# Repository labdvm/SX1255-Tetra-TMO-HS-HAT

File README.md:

# SX1255--HAT's

# Little PA HAT you can order from here:
- 

This is modified SXceiver, thanks to Tatu Peltola for shared schematic.
# Two versions of HAT's: HAT with (LPF_TX, BPF_RX filters and PA) and HAT with (LPF_TX, BPF_RX filters without PA) and added SPI line protection IC. The first HAT also is known as "Little PA".
# The PA (TQP3M9036) can amplify up to ~25dBm @ (70cm-band) 
# I can make Custom design too. (pclab.mk@gmail.com)
# RPi 4/5, fast-write micro-sd card or upgraded with M.2 nvme drive.
# The eeprom is for HW-ID " https://github.com/tejeez/sxxcvr/blob/main/dts/README.md ".
# For Tetra-TMO Base Station this is the installing procedures, " https://github.com/MidnightBlueLabs/tetra-bluestation-docs/wiki ".
# BlueStation, https://github.com/MidnightBlueLabs/tetra-bluestation
# BlueStation Tetra TMO configurator " https://bluestation.russel053.com/ "
# FlowStation, https://github.com/razvanzeces/flowstation
# Nexus-BS, https://github.com/invictus737/nexus-bs

Install FlowStation ---for sxceiver---
# 1. Install Trixie 64bit-LITE
2. Install lib's:
# sudo apt update
# sudo apt install git make g++ cmake
# sudo apt install libsoapysdr-dev
# sudo apt install soapysdr-tools
# sudo apt install libasound2-dev
# sudo apt install clang llvm-dev libclang-dev

3. Install Rust:
# curl https://sh.rustup.rs -sSf | sh

4. RPi-setup:
"enable SPI and I2C"
# sudo raspi-config > Interface Options > "enable and reboot the rpi"
# sudo nano /boot/firmware/config.txt
"add"
# dtparam=i2c_vc=on
"Reboot the Rpi"

5. Install SoapySX:
# cd
# git clone "https://github.com/tejeez/sxxcvr.git"
# cd sxxcvr/SoapySX
# mkdir build
# cd build
# cmake ..
# make
# sudo make install
# sudo ldconfig

Check that the driver is available:
# SoapySDRUtil --info

Check that the device is detected:
# ls -l /proc/device-tree/hat
# SoapySDRUtil --probe=driver=sx

6. Install The FlowStation:
# git clone https://github.com/razvanzeces/flowstation
# cd flowstation
# . "$HOME/.cargo/env"
# cargo build --release (or cargo build --release -j1)
# cp example_config/config.toml config.toml
# nano config.toml "configure the base station"
- After configured "config.toml" make a fallback copy
# cp config.toml config.toml.fallback

7. Run:
# cd flowstation
# ./target/release/bluestation-bs ./config.toml

8. Update:
# git pull
# cargo build --release

# Z32IT

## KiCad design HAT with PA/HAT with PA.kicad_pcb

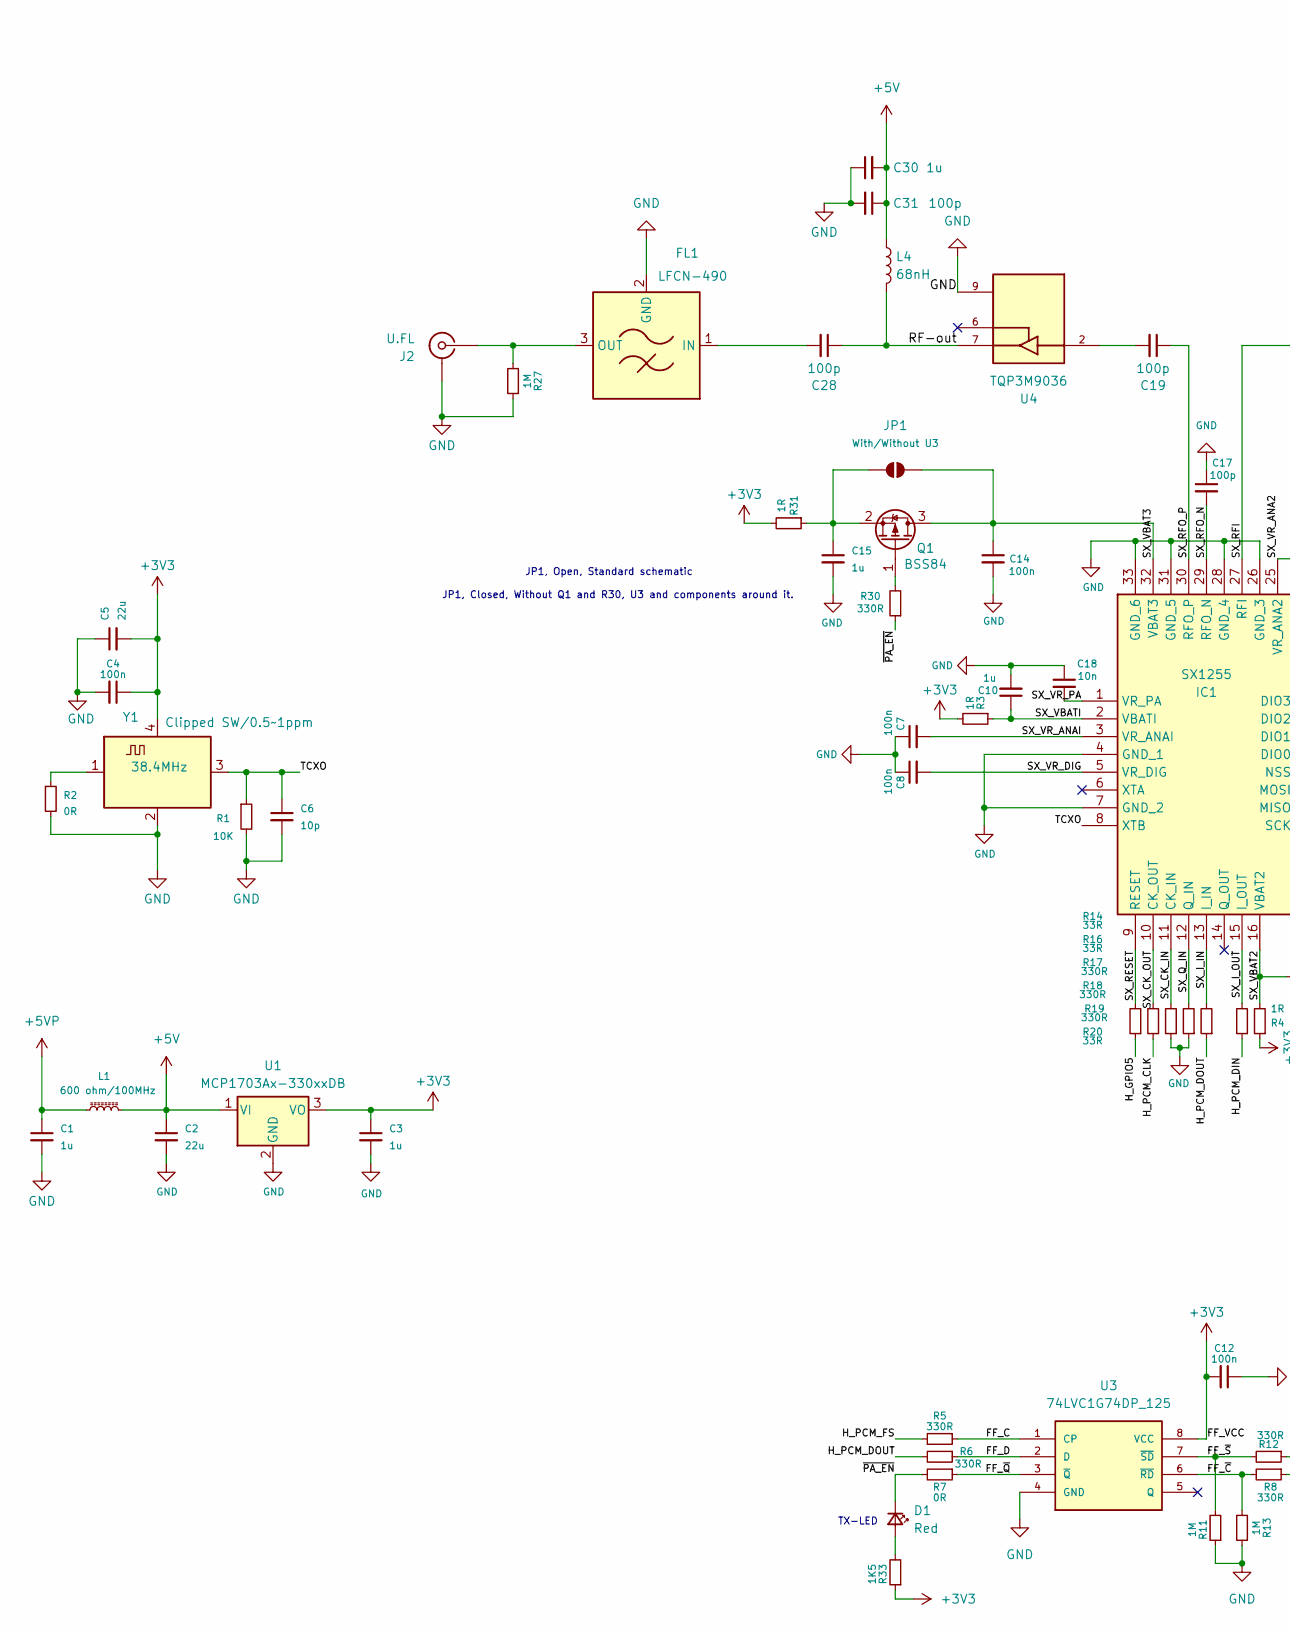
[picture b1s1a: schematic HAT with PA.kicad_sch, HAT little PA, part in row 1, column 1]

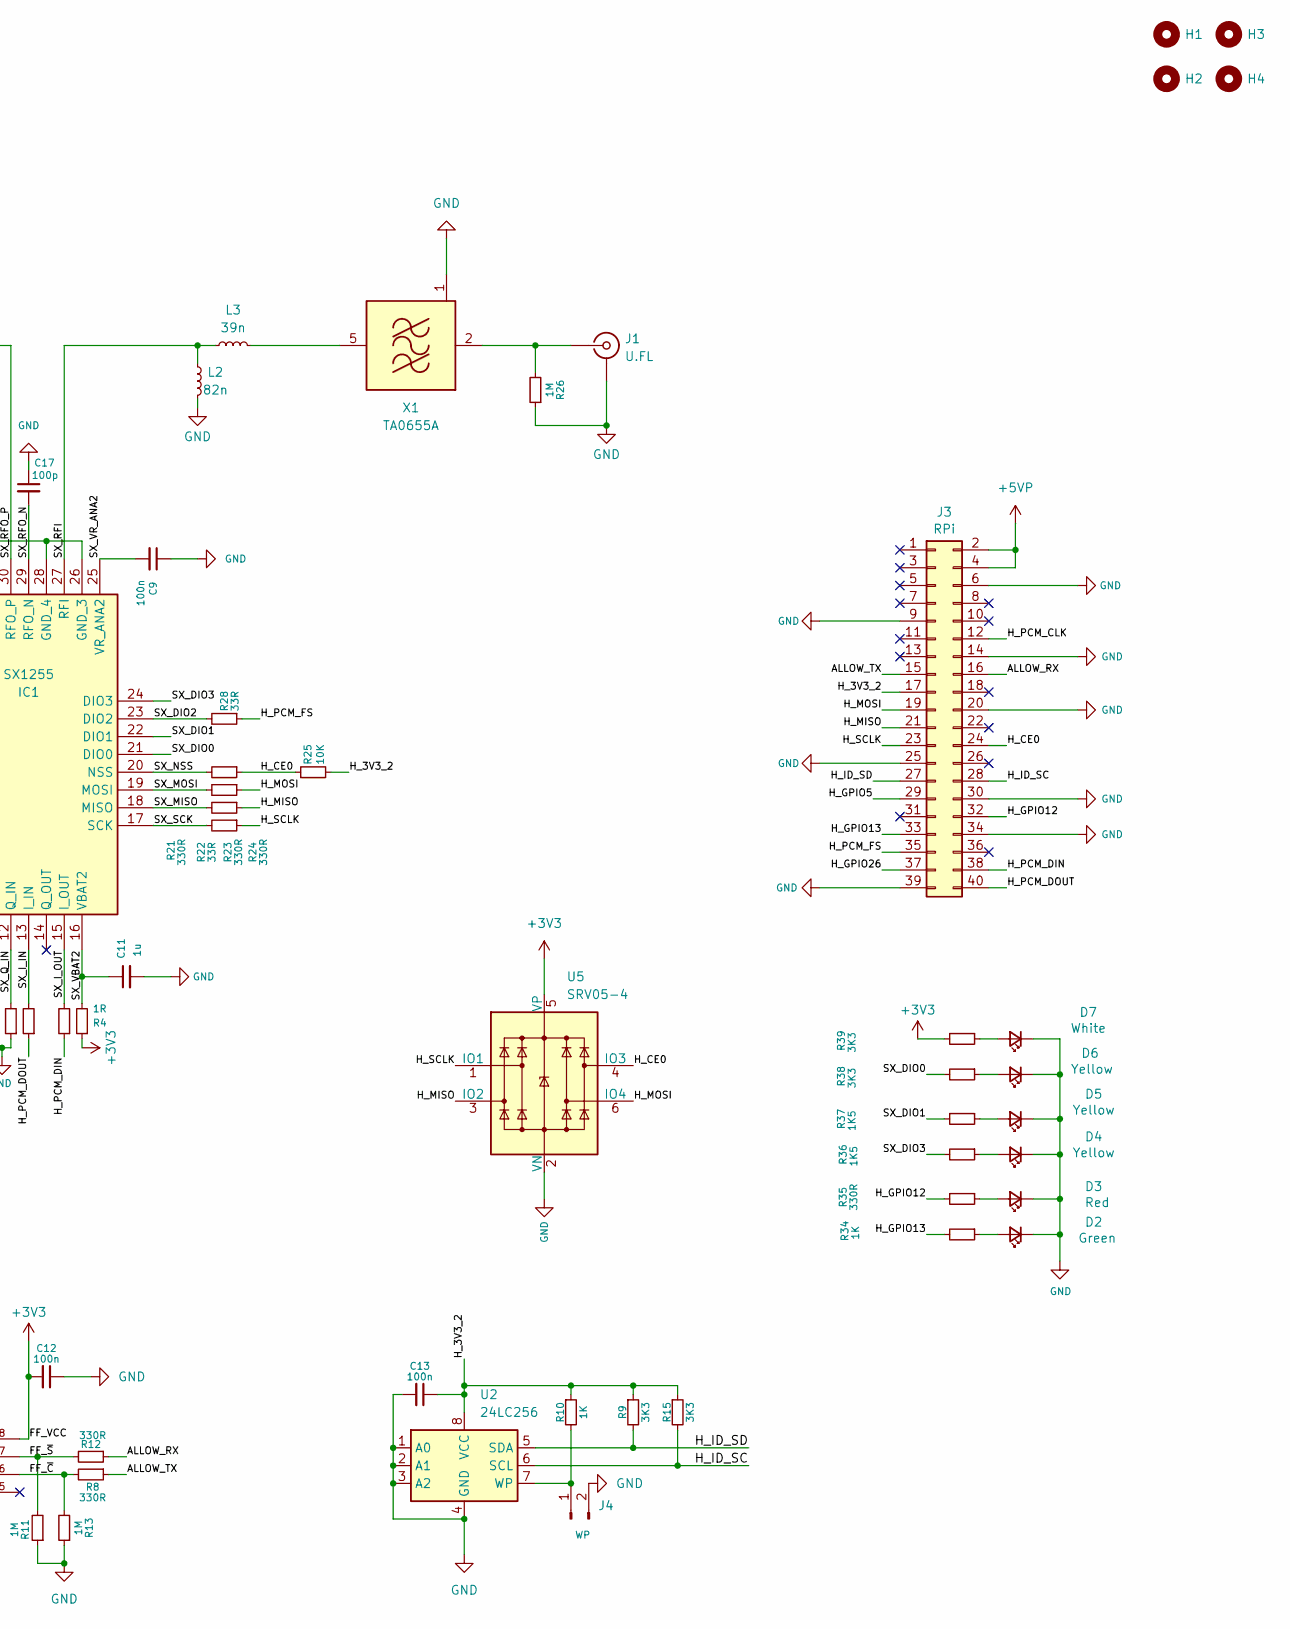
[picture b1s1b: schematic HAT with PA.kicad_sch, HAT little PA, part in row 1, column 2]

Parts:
C1, C3, C10, C11, C15, C30: 1u; C_0603_1608Metric; Part Number 311-3484-1-ND
C2, C5: 22u; C_1206_3216Metric; Part Number 1276-3148-1-ND
C4, C7, C8, C9, C12, C13, C14: 100n; C_0603_1608Metric; Part Number 720-1688-1-ND
C6: 10p; C_0603_1608Metric; Part Number 399-14932-1-ND
C17, C19, C28, C31: 100p; C_0603_1608Metric; Part Number 399-15348-1-ND
C18: 10n; C_0603_1608Metric; Part Number 399-C0603C103K8RACTUCT-ND
D1, D3: Red; LED_0603_1608Metric_Pad1.05x0.95mm_HandSolder; Part Number 160-1479-1-ND
D2: Green; LED_0603_1608Metric_Pad1.05x0.95mm_HandSolder; Part Number 754-APT1608SGD3CT-ND
D4, D5, D6: Yellow; LED_0603_1608Metric_Pad1.05x0.95mm_HandSolder; Part Number 160-1437-1-ND
D7: White; LED_0603_1608Metric_Pad1.05x0.95mm_HandSolder; Part Number 160-LTST-T180UWETCT-ND
FL1: LFCN-490; Filter_Mini-Circuits_FV1206; Part Number 3157-LFCN-490+CT-ND
H1, H2, H3, H4: MountingHole; MountingHole_2.7mm_M2.5_DIN965
IC1: SX1255; QFN50P500X500X80-33N-D; Part Number SX1255IWLTRTCT-ND
J1, J2: U.FL; Part Number 343-CONMHF1-SMD-G-TCT-ND
J3: RPi; PinSocket_2x20_P2.54mm_Vertical
J4: WP; PinHeader_1x02_P2.54mm_Vertical
JP1: With/Without U3; SolderJumper-2_P1.3mm_Open_RoundedPad1.0x1.5mm
L1: 600 ohm/100MHz; L_0805_2012Metric; Part Number 490-1046-1-ND
L2: 82n; L_0603_1608Metric; Part Number 712-LRC0603CJ82NGV001TCT-ND
L3: 39n; L_0603_1608Metric; Part Number 712-LRC0603CJ39NGV001TCT-ND
L4: 68nH; L_0603_1608Metric; Part Number 712-LRC0603CJ68NGV001TCT-ND
Q1: BSS84; SOT-23; Part Number 3372-BSS84TR-ND
R1, R25: 10K; R_0603_1608Metric; Part Number 541-10.0KHCT-ND
R2, R7: 0R; R_0603_1608Metric; Part Number 541-0.0GCT-ND
R3, R4, R31: 1R; R_0603_1608Metric; Part Number 541-1.00HHCT-ND
R5, R6, R8, R12, R17, R18, R19, R21, R23, R24, R30, R35: 330R; R_0603_1608Metric; Part Number 541-330HCT-ND
R9, R15, R38, R39: 3K3; R_0603_1608Metric; Part Number 541-3.30KHCT-ND
R10, R34: 1K; R_0603_1608Metric; Part Number 541-1.00KHCT-ND
R11, R13, R26, R27: 1M; R_0603_1608Metric; Part Number 541-1.00MHCT-ND
R14, R16, R20, R22, R28: 33R; R_0603_1608Metric; Part Number 541-33.0HCT-ND
R33, R36, R37: 1K5; R_0603_1608Metric; Part Number 541-1.5KGCT-ND
U1: MCP1703Ax-330xxDB; SOT-223-3_TabPin2; Part Number MCP1703T-3302E/DBCT-ND
U2: 24LC256; SOIC-8_3.9x4.9mm_P1.27mm; Part Number 24LC256-I/SN-ND
U3: 74LVC1G74DP_125; SOP65P400X110-8N; Part Number 1727-5983-1-ND
U4: TQP3M9036; SON50P200X200X95-9N; Part Number 2312-TQP3M9036CT-ND
U5: SRV05-4; SOT-23-6_Handsoldering; DigiKey Part Number SRV05-4CT-ND
X1: TA0655A; Filter_SAW-6_3.8x3.8mm
Y1: 38.4MHz; Crystal_SMD_3225-4Pin_3.2x2.5mm; Part Number 114-TG2520SMN38.4000M-MCGNNM3CT-ND

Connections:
+3V3: C3.1, C4.1, C5.2, C12.2, R3.2, R4.1, R31.2, R33.1, R39.2, U1.3 (VO), U3.8 (VCC), U5.5 (VP), Y1.4 (VDD)
+5V: C2.1, C30.2, C31.1, L1.2, L4.1, U1.1 (VI)
+5VP: C1.1, J3.2, J3.4, L1.1
/ALLOW_RX: J3.16, R12.1
/ALLOW_TX: J3.15, R8.1
/FF_C: R5.1, U3.1 (CP)
/FF_D: R6.1, U3.2 (D)
/FF_~C: R8.2, R13.2, U3.6 (~RD)
/FF_~Q: R7.1, U3.3 (~Q)
/FF_~S: R11.2, R12.2, U3.7 (~SD)
/H_3V3_2: C13.1, J3.17, R9.1, R10.1, R15.1, R25.2, U2.8 (VCC)
/H_CE0: J3.24, R24.1, R25.1, U5.4 (IO3)
/H_GPIO5: J3.29, R14.1
/H_GPIO12: J3.32, R35.2
/H_GPIO13: J3.33, R34.2
/H_GPIO26: J3.37
/H_ID_SC: J3.28, R15.2, U2.6 (SCL)
/H_ID_SD: J3.27, R9.2, U2.5 (SDA)
/H_MISO: J3.21, R22.1, U5.3 (IO2)
/H_MOSI: J3.19, R23.1, U5.6 (IO4)
/H_PCM_CLK: J3.12, R16.1
/H_PCM_DIN: J3.38, R20.1
/H_PCM_DOUT: J3.40, R6.2, R19.1
/H_PCM_FS: J3.35, R5.2, R28.1
/H_SCLK: J3.23, R21.1, U5.1 (IO1)
/RF-out: C28.1, L4.2, U4.7
/SX_CK_IN: IC1.11 (CK_IN), R17.2
/SX_CK_OUT: IC1.10 (CK_OUT), R16.2
/SX_DIO0: IC1.21 (DIO0), R38.2
/SX_DIO1: IC1.22 (DIO1), R37.2
/SX_DIO2: IC1.23 (DIO2), R28.2
/SX_DIO3: IC1.24 (DIO3), R36.2
/SX_I_IN: IC1.13 (I_IN), R19.2
/SX_I_OUT: IC1.15 (I_OUT), R20.2
/SX_MISO: IC1.18 (MISO), R22.2
/SX_MOSI: IC1.19 (MOSI), R23.2
/SX_NSS: IC1.20 (NSS), R24.2
/SX_Q_IN: IC1.12 (Q_IN), R18.2
/SX_RESET: IC1.9 (RESET), R14.2
/SX_RFI: IC1.27 (RFI), L2.2, L3.2
/SX_RFO_N: C17.2, IC1.29 (RFO_N)
/SX_RFO_P: C19.1, IC1.30 (RFO_P)
/SX_SCK: IC1.17 (SCK), R21.2
/SX_VBAT2: C11.1, IC1.16 (VBAT2), R4.2
/SX_VBAT3: C14.1, IC1.32 (VBAT3), JP1.2 (B), Q1.3 (D)
/SX_VBATI: C10.1, IC1.2 (VBATI), R3.1
/SX_VR_ANA2: C9.2, IC1.25 (VR_ANA2)
/SX_VR_ANAI: C7.2, IC1.3 (VR_ANAI)
/SX_VR_DIG: C8.2, IC1.5 (VR_DIG)
/SX_VR_PA: C18.2, IC1.1 (VR_PA)
/TCXO: C6.1, IC1.8 (XTB), R1.1, Y1.3 (OUT)
/~PA_EN: D1.1 (K), R7.2, R30.1
GND: C1.2, C2.2, C3.2, C4.2, C5.1, C6.2, C7.1, C8.1, C9.1, C10.2, C11.2, C12.1, C13.2, C14.2, C15.2, C17.1, C18.1, C30.1, C31.2, D2.1 (K), D3.1 (K), D4.1 (K), D5.1 (K), D6.1 (K), D7.1 (K), FL1.2 (GND), FL1.4 (GND), IC1.4 (GND_1), IC1.7 (GND_2), IC1.26 (GND_3), IC1.28 (GND_4), IC1.31 (GND_5), IC1.33 (GND_6), J1.2 (Ext), J2.2 (Ext), J3.6, J3.9, J3.14, J3.20, J3.25, J3.30, J3.34, J3.39, J4.2, L2.1, R1.2, R2.2, R11.1, R13.1, R17.1, R18.1, R26.1, R27.1, U1.2 (GND), U2.1 (A0), U2.2 (A1), U2.3 (A2), U2.4 (GND), U3.4 (GND), U4.1, U4.3, U4.4, U4.5, U4.8, U4.9, U4.V1, U4.V2, U4.V3, U5.2 (VN), X1.1 (GND), X1.3 (GND), X1.4 (GND), X1.6 (GND), Y1.2 (GND)
unnamed: C19.2, U4.2
unnamed: D1.2 (A), R33.2
unnamed: D2.2 (A), R34.1
unnamed: D3.2 (A), R35.1
unnamed: D4.2 (A), R36.1
unnamed: D5.2 (A), R37.1
unnamed: D6.2 (A), R38.1
unnamed: D7.2 (A), R39.1
unnamed: C28.2, FL1.1 (IN)
unnamed: FL1.3 (OUT), J2.1 (In), R27.2
unnamed: J1.1 (In), R26.2, X1.2 (IN)
unnamed: J4.1, R10.2, U2.7 (WP)
unnamed: C15.1, JP1.1 (A), Q1.2 (S), R31.1
unnamed: Q1.1 (G), R30.2
unnamed: L3.1, X1.5 (OUT)
unnamed: R2.1, Y1.1 (Tri-State)

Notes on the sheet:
JP1, Closed, Without Q1 and R30, U3 and components around it.
JP1, Open, Standard schematic
TX-LED

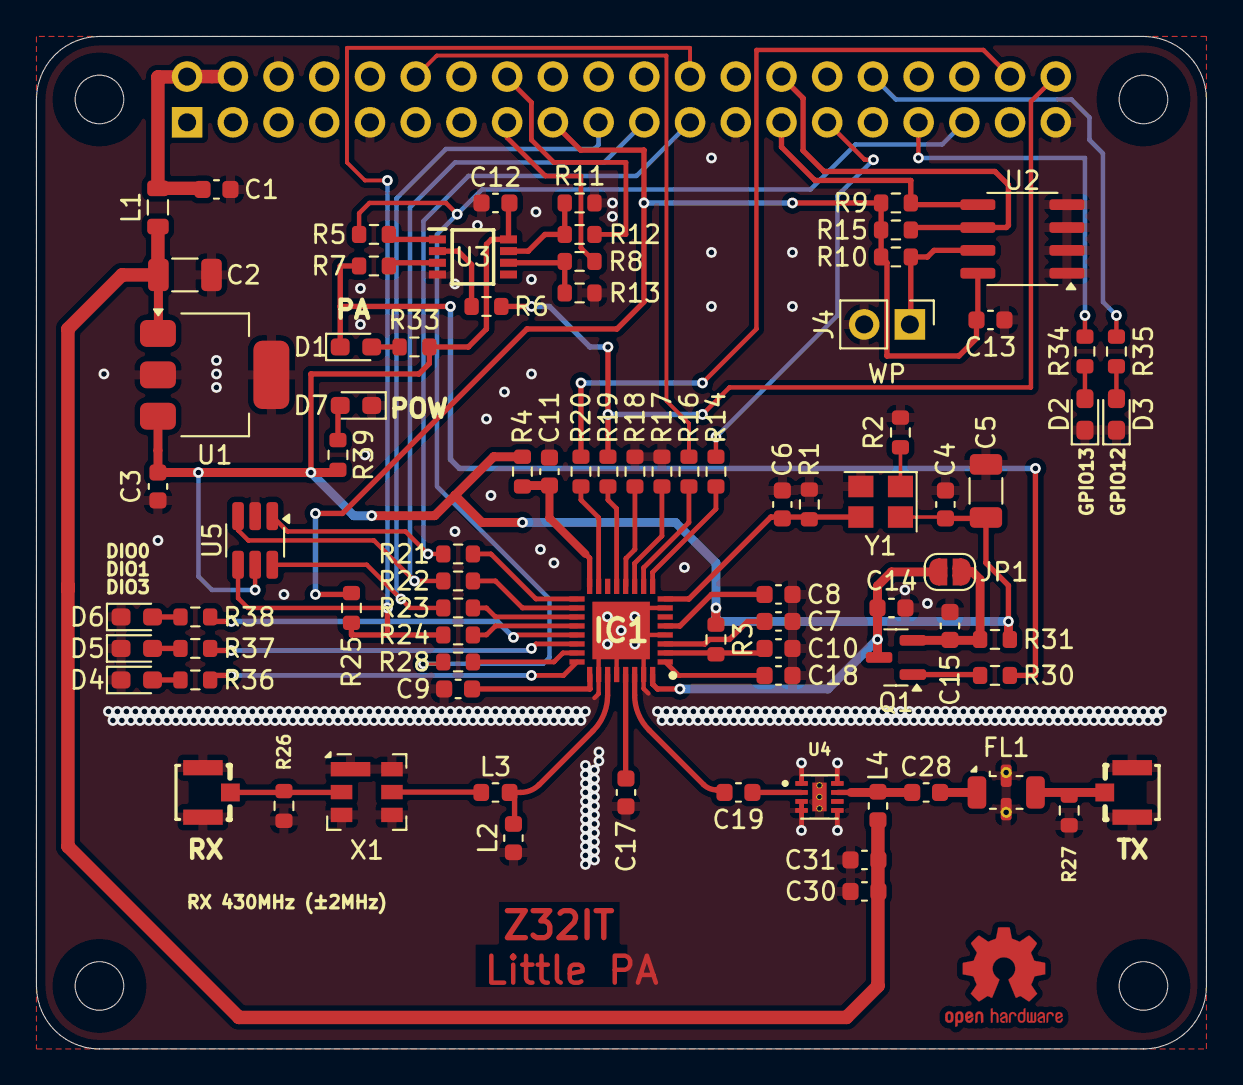
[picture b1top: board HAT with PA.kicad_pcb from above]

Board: 2 copper layers, 65.0 x 56.2 mm, 88 parts (1 on the bottom side), 68 nets.

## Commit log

2026-03-16 Revise README for SX1255-HAT details and credits
    Updated README to clarify SX1255-HAT versions and credit Tatu Peltola.
2026-03-16 Update HAT descriptions for clarity
    Clarified descriptions of the three versions of HATs for better readability.
2026-03-20 Update README to simplify RPi4/5 requirements
    Removed the mention of minimum RAM requirement for RPi4/5.
2026-03-24 Update README to reflect four versions of HAT
2026-03-25 Add custom design services note to README
    Added a note about custom design services.
2026-03-30 Update HAT versions description in README
2026-03-30 Update filter types in README for HAT versions
2026-03-30 Add donation information to README
    Added donation link for project support.
2026-04-10 Update BlueStation Tetra TMO configurator URL
2026-05-04 Update PA amplification value to 25dBm
2026-05-12 Update README with FlowStation installation steps
    Added installation instructions for FlowStation and related dependencies.
2026-05-14 Remove donation link from README
    Removed donation link from the README.
2026-06-02 Update README with additional information on HAT versions
    Added clarification about the first HAT being known as 'Little PA'.
2026-06-15 Revise README for installation steps and clarity
    Updated installation instructions and improved clarity in README.
2026-06-17 Update README to correct number of HAT versions
2026-06-17 Update Raspberry Pi version in README
2026-06-18 Update README with ordering information for Little PA HAT
    Added a link to order the Little PA HAT from PCBWay.
2026-06-22 Update README with config.toml fallback instructions
    Added instruction to create a fallback copy of config.toml
2026-06-22 Fix numbering in installation instructions
